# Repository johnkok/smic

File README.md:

# SMIC — 32-channel PDM microphone array and FPGA beamformer

SMIC is an experimental 32-microphone acoustic array built around Infineon
IM72D128V01 PDM microphones and a QMTECH Artix-7 XC7A100T core board. The
repository contains the circular microphone PCB, FPGA RTL, Vivado automation,
simulation testbenches, a C SPI control library, mechanical files, and the
manufacturer reference documents used for the design.

> [!CAUTION]
> The microphone PCB is fully routed, but it is not production-ready. KiCad
> 10.0.8 reports 19 ERC errors, one ERC warning, 32 DRC errors, and 15 DRC
> warnings. The current Gerbers represent the routed geometry but must not be
> fabricated until the footprint, sound-port clearance, bypassing, power/ground
> layout, BOM, and manufacturing release gates are resolved. See
> [SMIC PCB design review](Board/smic/docs/DESIGN_REVIEW.md).

The FPGA prototype has been synthesized, implemented, and loaded into an
XC7A100T, but external interfaces and production-quality audio have not received
complete timing, CDC, or laboratory validation.

## System overview

The intended signal chain is:

```mermaid
flowchart LR
    M[32 IM72D128V01 microphones<br/>16 edge-multiplexed PDM pairs]
    J[SMIC J1<br/>2x20, 1.27 mm]
    U4[QMTECH U4<br/>16 PDM inputs + clock]
    FE[PDM frontend<br/>CIC3 decimation]
    BC[32-channel delay-and-sum<br/>beam core]
    TX[I2S-like or two-slot<br/>audio transmitter]
    HOST[SPI host]
    REG[SPI registers]
    DAI[3.3 V DAI sink]

    M --> J --> U4 --> FE --> BC --> TX --> DAI
    HOST -->|SPI mode 0| REG --> BC
    REG --> TX
```

The FPGA uses a 12.288 MHz external audio reference to generate a 3.072 MHz PDM
clock, 48 kHz PCM samples, and a 3.072 MHz audio bit clock. Each PDM wire carries
two microphones selected on opposite clock edges, giving 32 logical channels
from 16 FPGA inputs.

## Repository layout

| Path | Contents |
|---|---|
| `Board/smic/smic/` | KiCad schematic, PCB, and project files |
| `Board/smic/docs/` | PCB review and exact acoustic-hole coordinates |
| `Board/smic/smic/Gerber/` | Current Gerber/drill export; blocked from fabrication by the design review |
| `FPGA/qmtech_beamformer/rtl/` | Synthesizable-intent SystemVerilog |
| `FPGA/qmtech_beamformer/constraints/` | XC7A100T and connector constraints |
| `FPGA/qmtech_beamformer/scripts/` | Vivado project, synthesis, implementation, and programming automation |
| `FPGA/qmtech_beamformer/sim/` | SPI and beam-core testbenches |
| `FPGA/qmtech_beamformer/host/` | C SPI API and steering helper |
| `FPGA/qmtech_beamformer/docs/` | Detailed FPGA integration notes |
| `Doc/` | QMTECH manuals, microphone datasheet, and array-placement drawing |
| `3D/` | FreeCAD enclosure model and SMIC Experiment workbench |

Generated Vivado projects, compatibility libraries, logs, bitstreams, and local
tool state are ignored and should not be committed.

## Current design status

| Area | Status |
|---|---|
| FPGA synthesis/implementation | Completes for `xc7a100tfgg676-1` with Vivado 2026.1 |
| FPGA SRAM programming | Tested through Vivado Hardware Manager/JTAG |
| FPGA configuration flash | N25Q064A SPIx4 erase/program/verify and flash boot tested; DONE=1 |
| Behavioral simulations | SPI and beam-core tests pass with Icarus Verilog 12 |
| Microphone hole geometry | All 32 NPTHs and back-silkscreen circles match the coordinate CSV |
| Microphone schematic nets | Pin 1 DATA, pin 3 CLOCK, and complementary SELECT pairing verified by source inspection |
| KiCad PCB routing | Fully connected: 954 segments, 287 through vias, three zones, and zero unconnected pads |
| KiCad ERC | **Fail:** 19 errors and one warning; paired PDM outputs need tri-state modeling, power intent and J1 NC need annotation, and the local U1 symbol library is unresolved |
| KiCad DRC | **Fail:** 32 microphone NPTH-to-pad clearance errors and 15 footprint-library mismatch warnings; zero unrouted items |
| Microphone PCB fabrication | **Blocked** pending footprint/clearance resolution, required bypassing, return-path review, released BOM/variant, clean checks, and complete manufacturing output |
| Audio quality | Prototype only; CIC compensation, anti-alias filtering, and protocol validation remain |
| DDR3 | Not instantiated |

## Experimental enclosure

[`3D/main_body.FCStd`](3D/main_body.FCStd) contains a derived
`SMICExperimentalBody` with a 6 mm-pitch internal thread spanning Z=0.8–49.2
mm. The original lower ledge is opened to the 128.4 mm threaded bore so a
bottom cap and separate threaded board-carrier rings can enter from either end.
The exterior uses 24 rounded vertical ribs as an initial wave texture.

The installed **SMIC Experiment** FreeCAD workbench makes the thread pitch,
depth, bore, axial range, bottom opening, and exterior wave count/radius/range
adjustable. Its checked-in source and installation instructions are in
[`3D/FreeCAD/Mod/SMIC_Experiment/`](3D/FreeCAD/Mod/SMIC_Experiment/README.md).
The generated body is a separate feature, leaving the original Part Design
body available for further edits.

[`3D/internal_ring_10mm.FCStd`](3D/internal_ring_10mm.FCStd) is a compatible
10 mm-high carrier ring with a 124 mm opening and 6 mm-pitch male thread. Its
128.0/132.0 mm minor/major diameters provide 0.2 mm radial clearance from the
body on each side, and each thread flank has an additional 0.2 mm axial
printing clearance. The aligned FreeCAD solids have zero interference. The
reproducible generator is [`3D/create_internal_ring.py`](3D/create_internal_ring.py).

### Not yet supplied

Replication still requires engineering work outside the checked-in artifacts:

- A released purchasing BOM with approved manufacturer part numbers.
- A production-reviewed microphone PCB: the current board is routed, but its
  ERC/DRC, microphone footprint, bypassing, return paths, and manufacturing
  package are not released.
- A keyed J1-to-U4 adapter PCB or a fully documented production cable drawing.
- A released enclosure, acoustic baffle, wind protection, mounting hardware,
  and a defined microphone-to-surface port geometry. The checked-in enclosure
  is an adjustable mechanical prototype, not a production release.
- Channel calibration data and a host steering implementation based on the
  actual Fermat coordinates.
- Production tests for supply current, J1 continuity, PDM channels, frequency
  response, noise, sensitivity matching, and beam pattern.
- A project license. No license file is currently present, so obtain permission
  before redistribution or commercial use.

## Required hardware

- QMTECH Artix-7 core board V01 with XC7A100T in the FGG676 package. Verify the
  marking on the fitted FPGA; do not assume another QMTECH variant has the same
  pinout.
- A compatible Xilinx/AMD JTAG programmer. The supplied script uses Vivado
  Hardware Manager, not OpenOCD.
- 32 genuine IM72D128V01 microphones and the remaining PCB components after a
  released BOM has been generated and reviewed.
- Regulated 3.3 V microphone-board supply with sufficient margin and a common
  ground with the FPGA.
- Low-jitter 12.288 MHz, 3.3 V clock source for QMTECH U2-18.
- A 3.3 V SPI controller or correctly selected bidirectional level translators.
- A 3.3 V-compatible DAI receiver, codec, logic analyzer, or oscilloscope.
- A keyed adapter/cable between SMIC J1 and QMTECH U4. Do not connect the two
  headers pin-for-pin; use the mapping below.

For bring-up, use a current-limited bench supply and verify every rail and clock
with an oscilloscope before fitting all microphones or attaching the FPGA.

## Hardware connections

### Complete bench wiring

```mermaid
flowchart TB
    PSU[Regulated 3.3 V supply]
    OSC[12.288 MHz<br/>3.3 V oscillator]
    JTAG[JTAG programmer]
    SPI[SPI controller]
    SINK[DAI receiver / logic analyzer]
    FPGA[QMTECH XC7A100T]
    MIC[SMIC microphone PCB]

    PSU -->|3.3 V: J1-37..40| MIC
    PSU ---|common ground| FPGA
    OSC -->|U2-18| FPGA
    JTAG -->|JTAG header| FPGA
    SPI <-->|U2 SPI, 3.3 V| FPGA
    FPGA -->|U2 BCLK / FS / SD| SINK
    FPGA -->|U4-21 to J1-2: PDM_CLK| MIC
    MIC -->|J1-6..36 even to U4-5..20: PDM_DATA| FPGA
```

All external interfaces in the current configuration are 3.3 V. QMTECH U2 is
in FPGA bank 15 and cannot be converted to 1.8 V by changing only the XDC
`IOSTANDARD`. A 1.8 V host requires physical translators.

### SMIC J1 to QMTECH U4

The adapter preserves channel order but changes pin numbering:

| Function | SMIC J1 | QMTECH U4 | FPGA pin | RTL port |
|---|---:|---:|---|---|
| PDM clock | 2 | 21 | F2 | `pdm_clk` |
| Pair 1 | 6 | 5 | B5 | `pdm_data[0]` |
| Pair 2 | 8 | 6 | A5 | `pdm_data[1]` |
| Pair 3 | 10 | 7 | B4 | `pdm_data[2]` |
| Pair 4 | 12 | 8 | A4 | `pdm_data[3]` |
| Pair 5 | 14 | 9 | A3 | `pdm_data[4]` |
| Pair 6 | 16 | 10 | A2 | `pdm_data[5]` |
| Pair 7 | 18 | 11 | D4 | `pdm_data[6]` |
| Pair 8 | 20 | 12 | C4 | `pdm_data[7]` |
| Pair 9 | 22 | 13 | C2 | `pdm_data[8]` |
| Pair 10 | 24 | 14 | B2 | `pdm_data[9]` |
| Pair 11 | 26 | 15 | E5 | `pdm_data[10]` |
| Pair 12 | 28 | 16 | D5 | `pdm_data[11]` |
| Pair 13 | 30 | 17 | C1 | `pdm_data[12]` |
| Pair 14 | 32 | 18 | B1 | `pdm_data[13]` |
| Pair 15 | 34 | 19 | E1 | `pdm_data[14]` |
| Pair 16 | 36 | 20 | D1 | `pdm_data[15]` |

J1 odd pins 1 through 35 are ground returns. J1-4 is not connected. J1-37
through J1-40 are the external 3.3 V input. U4 does not supply microphone-board
power: U4-3/4 are VCCO configuration points and U4-63/64 are `VIN`; neither is
an acceptable substitute for the separate regulated microphone supply.

### QMTECH U2: SPI, DAI, reset, and reference clock

| U2 | FPGA pin | Direction at FPGA | Function |
|---:|---|---|---|
| 20 | H21 | Input | SPI SCK |
| 6 | E26 | Input | SPI CS, active-low |
| 7 | D25 | Input | SPI MOSI |
| 8 | E25 | Output | SPI MISO |
| 9 | G26 | Output | Audio BCLK |
| 10 | H26 | Output | Audio frame sync |
| 11 | E23 | Output | Audio serial data |
| 12 | F23 | Input | Reset, active-low; internal pull-up |
| 18 | G20 | Input | External 12.288 MHz reference |

The onboard LEDs are active-low: D5 flashes at 1 Hz while the beamformer is
enabled, and D6 illuminates for at least 100 ms after a complete SPI access.

## Microphone PCB

### Geometry

The PCB is a two-layer, 1.6 mm circular design. The Edge.Cuts source circle is
centered at `(114.205281, 98.532588)` mm. Microphones follow the Fermat layout
shown in `Doc/DMIC_placement.jpeg`.

The IM72D128V01 PG-LLGA-5-3 recommendation uses a 0.8 mm acoustic hole at a
0.68 mm local-X offset from the package origin. Each package origin is shifted
to put its actual NPTH on the nominal Fermat point, and every DMIC body is
horizontal or vertical. All 32 NPTHs and their back-silkscreen circles match
[mic_acoustic_holes.csv](Board/smic/docs/mic_acoustic_holes.csv). Use those CSV
coordinates, not reference-designator origins, for calibration and beamforming.

### 3.3 V population

For direct compatibility with the FPGA:

- Do not populate U2 (`LP5907MFX-1.8`).
- Populate R18 as 0 ohm to use the existing regulator-bypass path.
- Supply exactly 3.3 V through J1-37..40.
- Never populate U2 and the R18 bypass simultaneously.

U1 is the 74FCT3807S clock fanout. R1 through R17 are 22 ohm series resistors;
the PCB contains 36 nominal 0.1 µF capacitors and two nominal 1 µF capacitors.
These values are a design summary, not a released purchasing BOM. Confirm
manufacturer part numbers, packages, ratings, availability, polarity, assembly
rules, and the exact U1 variant before ordering.

The two 1 µF parts do not satisfy the microphone datasheet's instruction to
place a 1 µF bypass capacitor close to each microphone VDD pad. This and the
U1 decoupling placement are production blockers, even though all power nets are
routed. The 74FCT3807S family supports 3.3 V, but an exact orderable TSSOP-20
part number must be selected.

### Current PCB review and required work

The current schematic-derived net assignments correctly connect IM72D128V01
pin 1 to paired DATA nets and pin 3 to U1 clock branches. Each of the 16 DATA
nets has two microphones with complementary SELECT straps. All ten U1 outputs
are used. The PCB has 954 track segments and 287 through vias, and KiCad reports
zero unconnected pads after zone refill.

Connectivity is not a production sign-off. KiCad 10.0.8 currently reports 19
ERC errors plus one warning and 32 DRC errors plus 15 warnings. The DRC errors
are the 0.18 mm copper-to-acoustic-NPTH clearance at all 32 microphones versus
the configured 0.25 mm minimum. The warnings are local microphone-footprint
library mismatches. The generated Gerbers and drills reflect this blocked
design and must not be ordered.

The detailed [schematic and PCB review](Board/smic/docs/DESIGN_REVIEW.md)
prioritizes these revisions before production release:

- create and freeze the correct project-local PG-LLGA-5-3 microphone footprint,
  then resolve the 32 acoustic-hole clearance errors with the fabricator;
- add the required 1 µF local bypassing at every microphone and move U1's four
  local capacitors directly to its supply/ground pairs;
- model the paired PDM outputs as tri-state, annotate power and no-connect
  intent, fix the missing local symbol-library mapping, and obtain clean ERC;
- preserve a continuous ground return, preferably with a four-layer stackup,
  instead of relying on the split B.Cu GND/3.3 V plane and stitching vias;
- review all ten clock branches, test-point stubs, and optional source damping
  using oscilloscope measurements rather than connectivity alone;
- add connector-side bulk capacitance and optional filtering/protection;
- key the board-to-FPGA interconnect and improve test access;
- add assembly fiducials plus enclosure-compatible mounting/tooling features;
- add a board revision, voltage/variant markings, approved MPNs, position files,
  and fabrication/assembly drawings.

These are design recommendations, not implemented hardware changes. Reassess
component placement and acoustic cavities against the enclosure before release.

### Manufacturing release checklist

1. Freeze the exact 3.3 V assembly variant, MPNs, project-local symbol library,
   and corrected PG-LLGA-5-3 footprint.
2. Add the required microphone/U1 bypassing and approve power/ground return
   paths, clock routing, connector protection, fiducials, and mechanics.
3. Resolve ERC by modeling real electrical intent; do not broadly exclude the
   paired PDM output errors.
4. Resolve every microphone hole-clearance finding with the fabricator, remove
   stale exclusions, refill zones, and obtain reviewed clean ERC/DRC results.
5. Re-verify J1 mapping, SELECT polarity, all clock destinations, and every
   acoustic NPTH against `mic_acoustic_holes.csv`.
6. Inspect solder-mask and paste apertures against the microphone datasheet.
7. Add revision/voltage/variant markings and complete fabrication, assembly,
   acoustic-port handling, and test specifications.
8. Generate schematic PDF, released BOM, position files, Gerbers, drills,
   Gerber job, and optional IPC-356 from one tagged revision.
9. Review all outputs in an independent viewer and compare their netlist and
   drill counts with the KiCad source.
10. Fabricate a small pilot batch, inspect ports and reflow, and test supply,
    clocks, all 16 PDM pairs, channel order, noise, calibration, and beam pattern
    before authorizing production quantity.

The checked-in `Board/smic/smic/Gerber/` directory was regenerated from the
current routed board, but it is explicitly blocked by the findings above and
must not yet be sent to a manufacturer.

## FPGA development

### Tool requirements

- AMD/Xilinx Vivado 2026.1 installed at `/opt/AMD_II/2026.1/Vivado`.
- Bash, Tcl, and standard Linux build utilities.
- Icarus Verilog 12 or another SystemVerilog simulator for the included tests.
- `curl`, `sha256sum`, and `dpkg-deb` only if the Ubuntu compatibility setup is
  needed.

To use another Vivado installation, edit `SMIC_VIVADO_ROOT` in
`FPGA/qmtech_beamformer/scripts/run_vivado.sh`.

### Run simulations

From the repository root:

```bash
iverilog -g2012 -s tb_spi -o /tmp/smic_tb_spi \
  FPGA/qmtech_beamformer/rtl/spi_regs.sv \
  FPGA/qmtech_beamformer/sim/tb_spi.sv
vvp /tmp/smic_tb_spi

iverilog -g2012 -s tb_beamformer -o /tmp/smic_tb_beamformer \
  FPGA/qmtech_beamformer/rtl/beam_core.sv \
  FPGA/qmtech_beamformer/sim/tb_beamformer.sv
vvp /tmp/smic_tb_beamformer
```

Both tests should print `PASS`. They cover register writes/commit/access and the
beam-core frame deadline, normalization, and integer delay path; they are not a
complete top-level, PDM, audio-protocol, timing, or CDC verification suite.

### Create, synthesize, and build

```bash
cd FPGA/qmtech_beamformer

# Only if Vivado reports missing legacy ncurses/tinfo libraries:
./scripts/setup_vivado_compat.sh

./scripts/run_vivado.sh -mode batch -source scripts/create_vivado_project.tcl
./scripts/run_vivado.sh -mode batch -source scripts/synthesize.tcl
./scripts/run_vivado.sh -mode batch -source scripts/build_bitstream.tcl
```

Review at least these generated reports before programming:

- `vivado_project/synth_utilization.rpt`
- `vivado_project/synth_timing_summary.rpt`
- `vivado_project/impl_utilization.rpt`
- `vivado_project/impl_timing_summary.rpt`
- `vivado_project/impl_drc.rpt`

The expected bitstream is
`vivado_project/qmtech_beamformer.runs/impl_1/beamformer_top.bit`.

### Program volatile FPGA SRAM

Connect exactly one compatible JTAG target, power the QMTECH board, then run:

```bash
cd FPGA/qmtech_beamformer
./scripts/run_vivado.sh -mode batch -source scripts/program_device.tcl
```

The script enumerates the chain, requires exactly one XC7A100T, programs the
bitstream, and reports DONE when that property is available. Programming is
volatile and is lost when power is removed.

### Program nonvolatile configuration flash

The QMTECH V01 board uses a 3.3 V Micron N25Q064A, 64 Mbit configuration flash.
The checked-in constraints generate a Master-SPIx4 bitstream matching the
board's `M[2:0]=100` boot straps. To replace the board's power-on image:

```bash
cd FPGA/qmtech_beamformer
./scripts/run_vivado.sh -mode batch -source scripts/generate_cfgmem.tcl
./scripts/run_vivado.sh -mode batch -source scripts/program_cfgmem.tcl
```

The programming script requires exactly one XC7A100T, loads Vivado's temporary
SPI bridge, erases the existing flash image, programs the MCS file, performs a
read-back verification, and boots the FPGA from flash. On 2026-11-15 the board
reported JEDEC ID `20 BA 17`, program/verify completed successfully, and the
flash-booted FPGA reported `DONE=1`.

## Operating the beamformer

### SPI protocol

- Use **SPI mode 0**: `CPOL=0`, `CPHA=0`. SCK idles low; the FPGA samples
  MOSI on rising edges and the host samples MISO on rising edges. Change data
  on falling edges.
- Use MSB first and keep SCK at or below 2 MHz. This conservative limit is for
  the current SCK-to-12.288-MHz toggle synchronizer, not the FPGA I/O limit.
- `CS_N` is active low. Hold it low for exactly 56 clocks and return it high
  between commands. MISO is high-impedance while `CS_N` is high, so the bus may
  be shared.
- Every command is exactly seven bytes:

```text
byte 0       byte 1..2             byte 3..6
opcode       16-bit address        32-bit data
0x02 write   big-endian            big-endian
0x03 read    big-endian            returned big-endian
```

For a write, opcode `0x02` is followed by the address and value. For a read,
send opcode `0x03`, the address, and four dummy bytes; the returned value is in
receive bytes 3 through 6. A command is accepted only after all 56 bits arrive.
The host transfer callback must keep `CS_N` active across the whole seven-byte
exchange and must not split it into separate opcode/address/data transfers.

Register writes cross asynchronously into the audio clock domain and normally
become visible within three 12.288 MHz clocks. Delay, gain, and polarity writes
go to shadow registers; writing `COMMIT.bit0=1` copies the complete set into the
beamformer together. Readback of those fields reports the shadow value. D6 is
held on for about 100 ms after every valid read or write transaction.

### Important registers

| Address | Name | Description |
|---:|---|---|
| `0x0000` | ID | Read-only, expected `0xBF320001` |
| `0x0004` | CTRL | Bit 0 enable, bit 1 mute |
| `0x0008` | STATUS | Placeholder |
| `0x000C` | SAMPLE_RATE | Read-only 48000 |
| `0x0010` | MODE | Bit 1 selects two-slot TDM-like output |
| `0x0014` | AZIMUTH | Reserved; host currently calculates delays |
| `0x0018` | ELEVATION | Reserved; host currently calculates delays |
| `0x001C` | OUTPUT_GAIN | Q1.15 |
| `0x0020` | ENABLE_MASK | One bit per microphone |
| `0x0024` | COMMIT | Write bit 0 to activate shadow delays, gains, and polarity |
| `0x0028` | FRAME_COUNT | Output frame counter |
| `0x002C` | ERRORS | Placeholder |
| `0x0030` | TEST_CONTROL | Test-source enable, routing, and pattern |
| `0x0034` | TEST_AMPLITUDE | Signed 24-bit synthetic PCM amplitude |
| `0x0038` | POLARITY_MASK | One invert bit per channel; shadowed by `COMMIT` |
| `0x0100 + 4*i` | DELAY[i] | Q16.16 samples, integer part limited to 254 |
| `0x0200 + 4*i` | GAIN[i] | Q1.15 microphone gain |
| `0x0300 + 4*i` | LEVEL[i] | Per-channel level |

`MODE.bit1` selects the two-slot TDM-like transmitter; zero selects I2S-like
framing. All other `MODE` bits are reserved and should be written as zero.
`OUTPUT_GAIN` and `GAIN[i]` use unsigned Q1.15 (`0x8000` = 1.0). Values up to
`0xFFFF` are valid, although headroom must be allowed to avoid output clipping.
Only `TEST_AMPLITUDE[23:0]` is used and it is interpreted as signed two's
complement; bits 31:24 are ignored and should be written as zero.
`LEVEL[i]` is the absolute magnitude of the most recently accepted PCM sample,
not RMS or peak-hold metering.

`TEST_CONTROL` is defined as follows:

| Bits | Meaning |
|---:|---|
| 0 | Enable synthetic PCM and bypass the PDM samples |
| 1 | Send the test signal to all channels; if zero, use the selected channel |
| 6:2 | Selected channel, 0 through 31 |
| 9:8 | Pattern: 0 = 1 kHz square, 1 = 1 kHz impulse train, 2 = DC, 3 = alternating samples (24 kHz) |
| Other | Reserved, write zero |

When test mode is enabled, unselected channels are forced to zero. The source
enters after PDM decimation but before history, fractional delay, calibration,
summation, and audio transmission. It therefore tests the beamformer and output
path, but does **not** test microphones, PDM wiring, CIC decimation, or acoustic
channel order.

### C host API

Implement `bf_spi_transfer`, initialize a `bf_device`, and call:

```c
bf_device dev = {
    .transfer = platform_spi_transfer,
    .ctx = &platform_context,
};

bf_init(&dev, array_radius_m);
bf_set_geometry(&dev, measured_positions);
bf_set_calibration(&dev, measured_calibration);
bf_set_direction(&dev, azimuth_deg, elevation_deg);
bf_start(&dev);
```

`bf_init()` supplies a circular fallback geometry only. The PCB is a Fermat
spiral, so production software must build a 32-element `bf_mic_position` array
from `Board/smic/docs/mic_acoustic_holes.csv`, convert millimetres to metres,
subtract the array centre, choose whether acoustic +Y is KiCad +Y or -Y, and
call `bf_set_geometry()`. The `MKn` number is treated as channel `n-1` by the
heatmap tool, but that assumption must be verified against the physical PDM
pair/edge channel order before use.

The host library stores per-channel gain, delay correction, and polarity in
`bf_mic_calibration`. `bf_set_direction()` combines those values with geometric
steering, writes all shadow registers, writes the polarity mask, then commits
the set. These values are volatile: reload geometry and calibration after every
FPGA reset or power cycle.

### Steering mathematics

Angles use degrees. Azimuth is measured in the array XY plane from +X toward
+Y; elevation is measured from the XY plane toward +Z. The look-direction unit
vector is

```text
u = [cos(el) cos(az), cos(el) sin(az), sin(el)].
```

For microphone position `r_i=[x_i,y_i,z_i]`, sample rate `Fs=48000`, and speed
of sound `c` (343 m/s by default), the host first calculates

```text
p_i       = dot(r_i, u)
raw_i     = -Fs * p_i / c + calibration_delay_i
d_i       = raw_i - min(raw_0 ... raw_31)
DELAY[i]  = round(65536 * d_i)
GAIN[i]   = round(32768 * calibration_gain_i)
```

Subtracting the common minimum makes every hardware delay non-negative without
changing relative phase. `d_i` must be at most 254 samples. At 48 kHz that is
5.29 ms, much longer than the geometric delay across this PCB. Temperature
changes `c`; for tighter steering, use approximately
`c = 331.3 + 0.606*T_C` m/s or a measured local value.

Inside `beam_core.sv`, the integer and fractional portions select two adjacent
history samples. With `f=DELAY[i][15:0]/65536`, interpolation is

```text
x_i' = (1-f) * history_i[n-floor(d_i)]
       + f * history_i[n-floor(d_i)-1]
y    = OUTPUT_GAIN * (sum(enabled_i * polarity_i * GAIN[i] * x_i') / N)
```

`N` is the number of enabled microphones and division uses a Q0.24 reciprocal
lookup table. The final value is saturated to signed 24-bit PCM. Linear
interpolation is inexpensive but its high-frequency magnitude/phase error is
larger than a Farrow or windowed-sinc fractional-delay filter.

### Beam heatmap

The FPGA produces one audio beam; it does not render or scan a heatmap. The
far-field prediction is implemented on the host in
[`beam_heatmap.py`](FPGA/qmtech_beamformer/host/beam_heatmap.py). It uses the
actual acoustic-hole coordinates, the same steering-delay equation, optional
calibration, and the narrow-band array factor at a chosen frequency. Run:

```bash
python3 FPGA/qmtech_beamformer/host/beam_heatmap.py \
  --geometry Board/smic/docs/mic_acoustic_holes.csv \
  --calibration FPGA/qmtech_beamformer/host/calibration.example.csv \
  --frequency 3000 --steer-az 45 --steer-el 0 \
  --output /tmp/smic_3khz
```

This writes `/tmp/smic_3khz.csv` in dB and a directly viewable
`/tmp/smic_3khz.svg`. By default KiCad Y is negated so +Y points upward in a
top-view Cartesian plot; pass `--keep-kicad-y` to retain KiCad's Y direction.
The result is a theoretical free-field map, not measured acoustic performance:
it omits enclosure diffraction, microphone directivity, tolerances, reflections,
and the CIC response. A broadband beam must be assessed at several frequencies.

### Digital test mode

Use test mode before attaching the microphone PCB to check SPI, shadow commits,
delay/gain/polarity processing, DAI, and the receiver:

```c
/* 0x040000 is about -30 dBFS in signed 24-bit PCM. */
bf_set_test_mode(&dev, BF_TEST_SQUARE_1KHZ, 0, 1, 0x040000);
bf_start(&dev);
/* Inspect audio output, then always return to real PDM input. */
bf_disable_test_mode(&dev);
```

With `all_channels=1` and zero delays, output amplitude should equal the test
amplitude because the core normalizes by enabled-channel count. Select a single
channel and set `ENABLE_MASK` to the same one bit to test that channel's delay,
gain, and polarity without the other 31 zeros reducing the result. The impulse
pattern is useful for confirming integer/fractional delay. DC is intended for
short datapath checks and should not be sent to speakers at high amplitude.

### Microphone calibration guide

Calibration support is manual/offline; the design does not yet estimate
coefficients automatically. A practical procedure is:

1. Verify channel order first with a close sound source at each microphone.
   Record the FPGA channel corresponding to every `MKn`; do not infer it only
   from connector numbering or shared PDM data pairs.
2. Place the completed array and a reference loudspeaker in a low-reflection
   setup, aimed normal to the PCB and far enough away that path differences are
   small. Keep source, gain, and geometry fixed.
3. Capture every decimated microphone channel using an FPGA diagnostic build or
   external logic. The current mono audio output and instantaneous `LEVEL[i]`
   registers are not sufficient for accurate phase calibration.
4. Play a band-limited sweep or maximum-length sequence. Estimate relative lag
   by cross-correlation around the expected geometric lag. Choose a reference
   channel and store each residual in `delay_samples`; fractional values are
   supported.
5. Compare RMS amplitudes over the same steady segment. Set
   `gain_linear_i = target_rms / measured_rms_i`, then reduce all gains by a
   common factor if any would reach 2.0. Use `invert=1` only when correlation
   shows a true 180-degree polarity reversal.
6. Save 32 rows using the format in
   [`calibration.example.csv`](FPGA/qmtech_beamformer/host/calibration.example.csv),
   load them into `bf_mic_calibration`, call `bf_set_calibration()`, and then
   call `bf_set_direction()` to write and commit the combined coefficients.
7. Repeat the measurement from several directions and across the operating
   band. A delay that changes strongly with frequency indicates acoustic or
   filter mismatch that a single delay/gain coefficient cannot correct.

Calibration delay is a correction applied by the FPGA. If a channel is measured
late by `q` samples, store approximately `-q` for that channel; removal of the
common minimum then delays the other channels by the equivalent amount. If it
is early by `q`, store approximately `+q`. Confirm this sign convention with an
impulse or correlation before saving coefficients. Negative values are accepted
as long as the final relative delays fit the 254-sample history limit.

### Audio output

The output uses 64 bit clocks per 48 kHz frame. Mode bit 1 selects between an
I2S-like framing mode and a TDM-like two-slot mode. Only one mono beam is emitted
in slot 0; slot 1 is zero. Validate BCLK, frame-sync polarity, sample alignment,
and one-bit I2S delay against the actual receiver before relying on the stream.

## Signal-processing architecture and limitations

- PDM decimation is CIC3 at a factor of 64. It requires a compensation and
  anti-alias FIR for production-quality audio.
- The beamformer uses a time-multiplexed 8192x24 history memory and completes a
  frame in 195 of the 256 available 12.288 MHz clocks.
- Fractional delay uses an initial linear method; a verified higher-quality
  interpolator is still required.
- There is no AEC, AGC, automatic microphone calibration, MVDR, source tracking,
  or multiple simultaneous beams.
- The planar array cannot uniquely resolve elevation sign and may exhibit
  front/back ambiguity depending on its acoustic mounting.
- External I/O delays and complete CDC constraints are not signed off.
- DDR3 is intentionally unused because the present history is only 24 KiB.
  DDR3 is a future option for capture buffers, longer delays, diagnostics, or
  multiple beams and requires a board-specific MIG configuration.

## Bring-up sequence

1. Resolve the production-review blockers and manufacture only a tagged,
   reviewed microphone PCB; do not use the current blocked Gerbers.
2. With U2 absent and R18 fitted, power only the microphone PCB from a
   current-limited 3.3 V supply. Verify resistance-to-ground before power and
   then verify the rail at U1 and several microphones.
3. Apply the PDM clock independently and confirm all fanout outputs before
   attaching the FPGA data inputs.
4. Verify J1 pin 1, cable orientation, and every continuity path to U4.
5. Program the FPGA with the microphone PCB disconnected and confirm D5/D6,
   SPI ID access, clock, reset, and DAI outputs.
6. Connect one microphone pair first. Confirm clock amplitude, DATA high-Z edge
   behavior, channel polarity, and PCM activity.
7. Add the remaining pairs while monitoring supply current and signal integrity.
8. Measure channel order using a local acoustic stimulus and compare it with the
   CSV geometry before enabling beam steering.
9. Capture known signals, check clipping/noise/CIC droop, and calibrate gain and
   delay before evaluating beam patterns.

## Primary references

- [FPGA integration and limitations](FPGA/qmtech_beamformer/docs/INTEGRATION.md)
- [Microphone PCB review](Board/smic/docs/DESIGN_REVIEW.md)
- [Exact acoustic-hole coordinates](Board/smic/docs/mic_acoustic_holes.csv)
- `Doc/infineon_im72d128_datasheet_en.pdf`
- `Doc/QMTECH_Artix-7_XC7A100T_Core_Board_User_Manual(Hardware)_V01.pdf`
- `Doc/QMTECH_XC7A75T_100T_200T-CORE-BOARD-V01-20210109.pdf`

Before changing connector assignments, voltage levels, the FPGA part, or the
microphone footprint, recheck the original manufacturer documents rather than
copying values from this README alone.

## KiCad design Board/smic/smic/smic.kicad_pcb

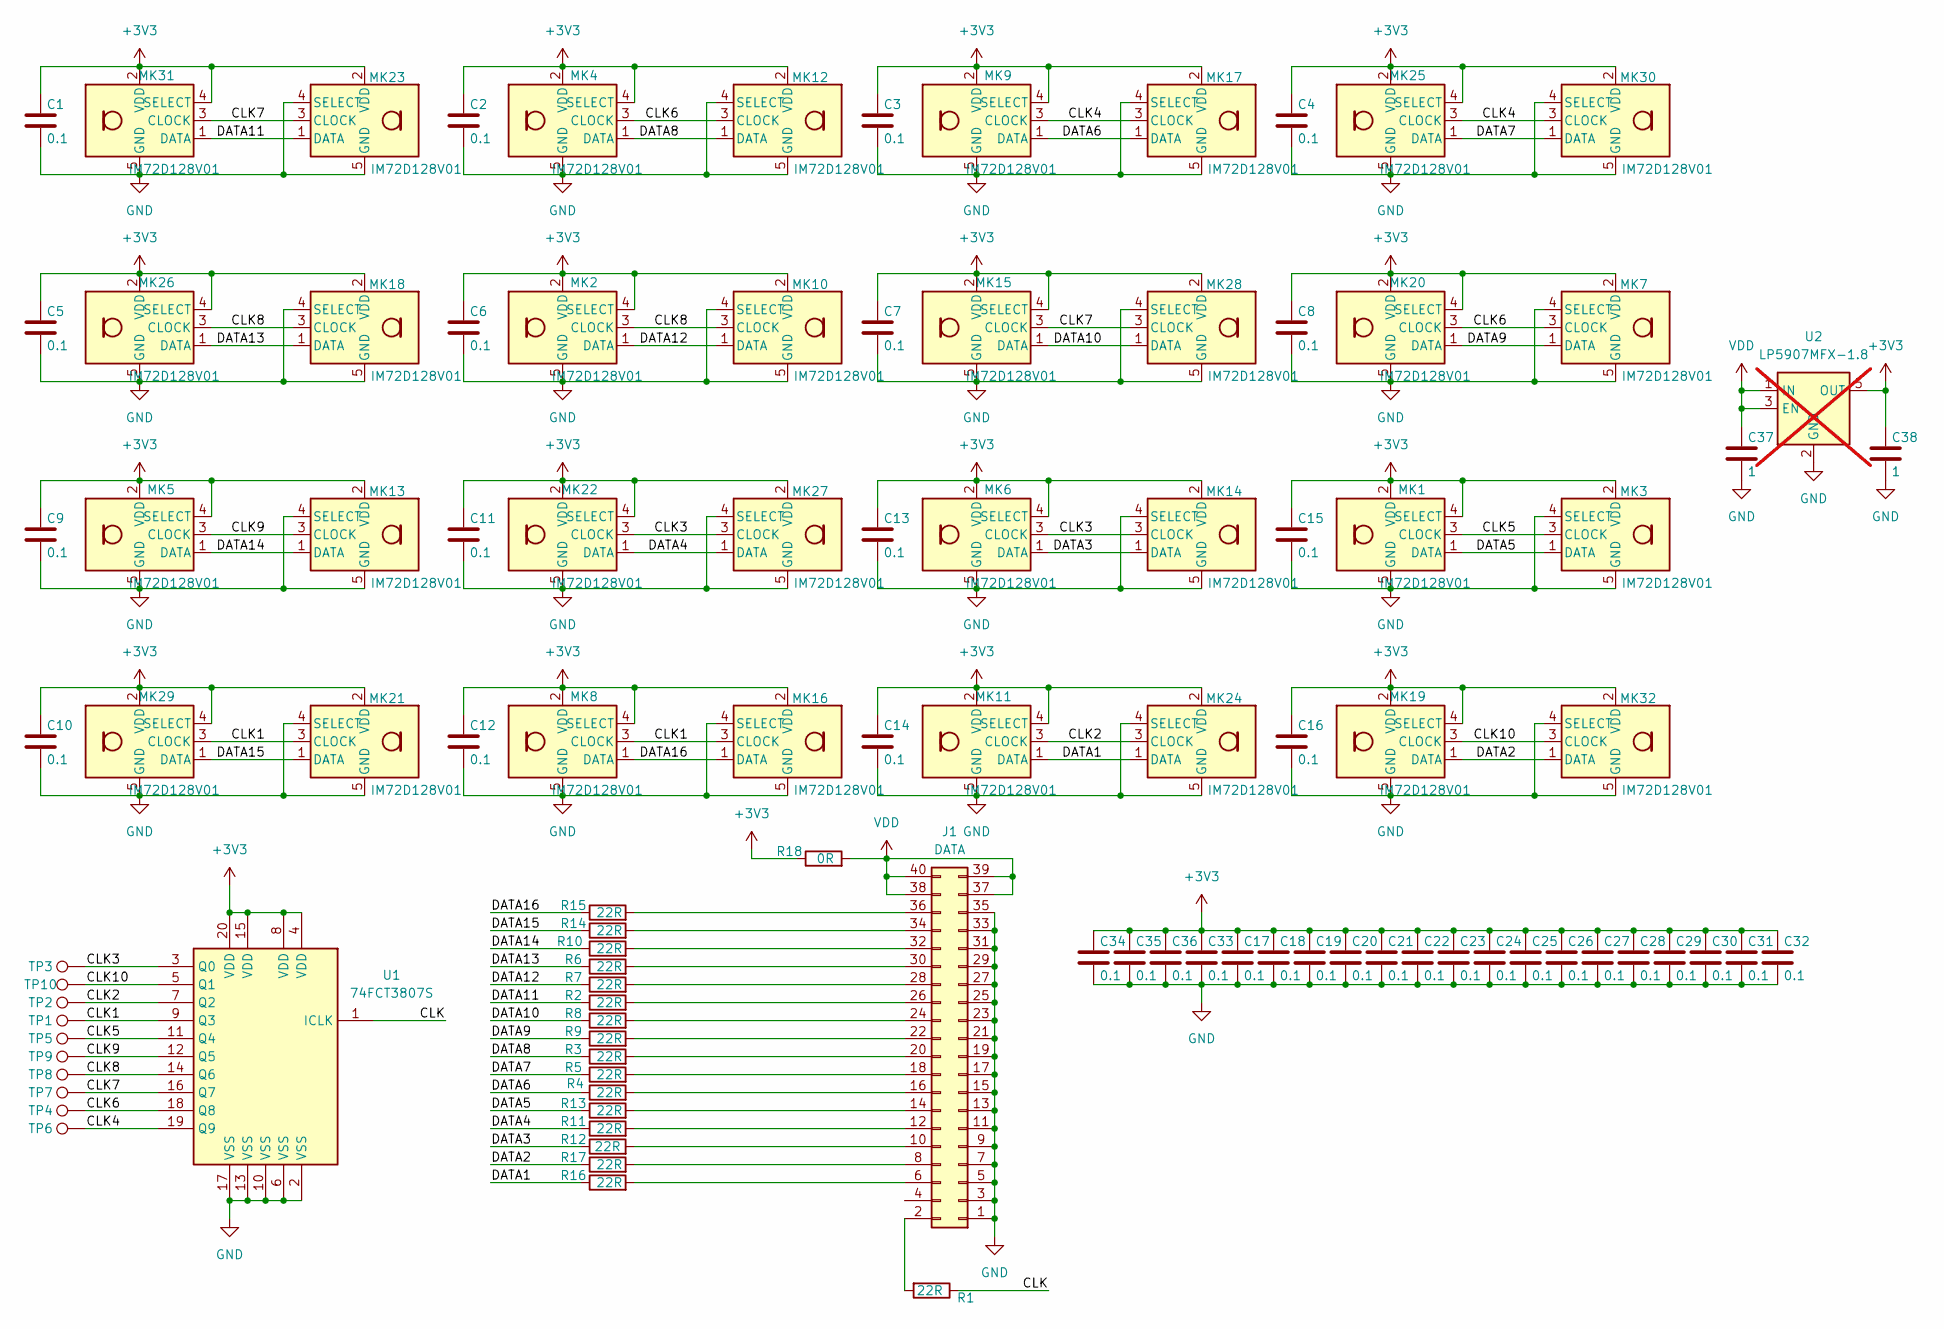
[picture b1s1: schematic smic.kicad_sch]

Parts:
C1, C2, C3, C4, C5, C6, C7, C8, C9, C10, C11, C12, C13, C14, C15, C16, C17, C18, C19, C20, C21, C22, C23, C24, C25, C26, C27, C28, C29, C30, C31, C32, C33, C34, C35, C36: 0.1; C_0603_1608Metric
C37, C38: 1; C_0805_2012Metric_Pad1.18x1.45mm_HandSolder
J1: DATA; PinHeader_2x20_P1.27mm_Vertical_SMD
MK1, MK2, MK3, MK4, MK5, MK6, MK7, MK8, MK9, MK10, MK11, MK12, MK13, MK14, MK15, MK16, MK17, MK18, MK19, MK20, MK21, MK22, MK23, MK24, MK25, MK26, MK27, MK28, MK29, MK30, MK31, MK32: IM72D128V01; Infineon_PG-LLGA-5-2
R1, R2, R3, R4, R5, R6, R7, R8, R9, R10, R11, R12, R13, R14, R15, R16, R17: 22R; R_0603_1608Metric_Pad0.98x0.95mm_HandSolder
R18: 0R; R_1206_3216Metric_Pad1.30x1.75mm_HandSolder
TP1, TP2, TP3, TP4, TP5, TP6, TP7, TP8, TP9, TP10: TestPoint_Pad_D1.5mm
U1: 74FCT3807S; TSSOP-20_4.4x6.5mm_P0.65mm
U2: LP5907MFX-1.8; SOT-23-5; not fitted

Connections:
+3V3: C1.2, C2.2, C3.2, C4.2, C5.2, C6.2, C7.2, C8.2, C9.2, C10.2, C11.2, C12.2, C13.2, C14.2, C15.2, C16.2, C17.2, C18.2, C19.2, C20.2, C21.2, C22.2, C23.2, C24.2, C25.2, C26.2, C27.2, C28.2, C29.2, C30.2, C31.2, C32.2, C33.2, C34.2, C35.2, C36.2, C38.2, MK1.2 (VDD), MK1.4 (SELECT), MK2.2 (VDD), MK2.4 (SELECT), MK3.2 (VDD), MK4.2 (VDD), MK4.4 (SELECT), MK5.2 (VDD), MK5.4 (SELECT), MK6.2 (VDD), MK6.4 (SELECT), MK7.2 (VDD), MK8.2 (VDD), MK8.4 (SELECT), MK9.2 (VDD), MK9.4 (SELECT), MK10.2 (VDD), MK11.2 (VDD), MK11.4 (SELECT), MK12.2 (VDD), MK13.2 (VDD), MK14.2 (VDD), MK15.2 (VDD), MK15.4 (SELECT), MK16.2 (VDD), MK17.2 (VDD), MK18.2 (VDD), MK19.2 (VDD), MK19.4 (SELECT), MK20.2 (VDD), MK20.4 (SELECT), MK21.2 (VDD), MK22.2 (VDD), MK22.4 (SELECT), MK23.2 (VDD), MK24.2 (VDD), MK25.2 (VDD), MK25.4 (SELECT), MK26.2 (VDD), MK26.4 (SELECT), MK27.2 (VDD), MK28.2 (VDD), MK29.2 (VDD), MK29.4 (SELECT), MK30.2 (VDD), MK31.2 (VDD), MK31.4 (SELECT), MK32.2 (VDD), R18.1, U1.4 (VDD), U1.8 (VDD), U1.15 (VDD), U1.20 (VDD), U2.5 (OUT)
/CLK: R1.1, U1.1 (ICLK)
/CLK1: MK8.3 (CLOCK), MK16.3 (CLOCK), MK21.3 (CLOCK), MK29.3 (CLOCK), TP1.1 (1_1), U1.9 (Q3)
/CLK2: MK11.3 (CLOCK), MK24.3 (CLOCK), TP2.1 (1_1), U1.7 (Q2)
/CLK3: MK6.3 (CLOCK), MK14.3 (CLOCK), MK22.3 (CLOCK), MK27.3 (CLOCK), TP3.1 (1_1), U1.3 (Q0)
/CLK4: MK9.3 (CLOCK), MK17.3 (CLOCK), MK25.3 (CLOCK), MK30.3 (CLOCK), TP6.1 (1_1), U1.19 (Q9)
/CLK5: MK1.3 (CLOCK), MK3.3 (CLOCK), TP5.1 (1_1), U1.11 (Q4)
/CLK6: MK4.3 (CLOCK), MK7.3 (CLOCK), MK12.3 (CLOCK), MK20.3 (CLOCK), TP4.1 (1_1), U1.18 (Q8)
/CLK7: MK15.3 (CLOCK), MK23.3 (CLOCK), MK28.3 (CLOCK), MK31.3 (CLOCK), TP7.1 (1_1), U1.16 (Q7)
/CLK8: MK2.3 (CLOCK), MK10.3 (CLOCK), MK18.3 (CLOCK), MK26.3 (CLOCK), TP8.1 (1_1), U1.14 (Q6)
/CLK9: MK5.3 (CLOCK), MK13.3 (CLOCK), TP9.1 (1_1), U1.12 (Q5)
/CLK10: MK19.3 (CLOCK), MK32.3 (CLOCK), TP10.1 (1_1), U1.5 (Q1)
/DATA1: MK11.1 (DATA), MK24.1 (DATA), R16.1
/DATA2: MK19.1 (DATA), MK32.1 (DATA), R17.1
/DATA3: MK6.1 (DATA), MK14.1 (DATA), R12.1
/DATA4: MK22.1 (DATA), MK27.1 (DATA), R11.1
/DATA5: MK1.1 (DATA), MK3.1 (DATA), R13.1
/DATA6: MK9.1 (DATA), MK17.1 (DATA), R4.1
/DATA7: MK25.1 (DATA), MK30.1 (DATA), R5.1
/DATA8: MK4.1 (DATA), MK12.1 (DATA), R3.1
/DATA9: MK7.1 (DATA), MK20.1 (DATA), R9.1
/DATA10: MK15.1 (DATA), MK28.1 (DATA), R8.1
/DATA11: MK23.1 (DATA), MK31.1 (DATA), R2.1
/DATA12: MK2.1 (DATA), MK10.1 (DATA), R7.1
/DATA13: MK18.1 (DATA), MK26.1 (DATA), R6.1
/DATA14: MK5.1 (DATA), MK13.1 (DATA), R10.1
/DATA15: MK21.1 (DATA), MK29.1 (DATA), R14.1
/DATA16: MK8.1 (DATA), MK16.1 (DATA), R15.1
GND: C1.1, C2.1, C3.1, C4.1, C5.1, C6.1, C7.1, C8.1, C9.1, C10.1, C11.1, C12.1, C13.1, C14.1, C15.1, C16.1, C17.1, C18.1, C19.1, C20.1, C21.1, C22.1, C23.1, C24.1, C25.1, C26.1, C27.1, C28.1, C29.1, C30.1, C31.1, C32.1, C33.1, C34.1, C35.1, C36.1, C37.1, C38.1, J1.1, J1.3, J1.5, J1.7, J1.9, J1.11, J1.13, J1.15, J1.17, J1.19, J1.21, J1.23, J1.25, J1.27, J1.29, J1.31, J1.33, J1.35, MK1.5 (GND), MK2.5 (GND), MK3.4 (SELECT), MK3.5 (GND), MK4.5 (GND), MK5.5 (GND), MK6.5 (GND), MK7.4 (SELECT), MK7.5 (GND), MK8.5 (GND), MK9.5 (GND), MK10.4 (SELECT), MK10.5 (GND), MK11.5 (GND), MK12.4 (SELECT), MK12.5 (GND), MK13.4 (SELECT), MK13.5 (GND), MK14.4 (SELECT), MK14.5 (GND), MK15.5 (GND), MK16.4 (SELECT), MK16.5 (GND), MK17.4 (SELECT), MK17.5 (GND), MK18.4 (SELECT), MK18.5 (GND), MK19.5 (GND), MK20.5 (GND), MK21.4 (SELECT), MK21.5 (GND), MK22.5 (GND), MK23.4 (SELECT), MK23.5 (GND), MK24.4 (SELECT), MK24.5 (GND), MK25.5 (GND), MK26.5 (GND), MK27.4 (SELECT), MK27.5 (GND), MK28.4 (SELECT), MK28.5 (GND), MK29.5 (GND), MK30.4 (SELECT), MK30.5 (GND), MK31.5 (GND), MK32.4 (SELECT), MK32.5 (GND), U1.2 (VSS), U1.6 (VSS), U1.10 (VSS), U1.13 (VSS), U1.17 (VSS), U2.2 (GND)
unnamed: J1.2, R1.2
unnamed: J1.6, R16.2
unnamed: J1.8, R17.2
unnamed: J1.10, R12.2
unnamed: J1.12, R11.2
unnamed: J1.14, R13.2
unnamed: J1.16, R4.2
unnamed: J1.18, R5.2
unnamed: J1.20, R3.2
unnamed: J1.22, R9.2
unnamed: J1.24, R8.2
unnamed: J1.26, R2.2
unnamed: J1.28, R7.2
unnamed: J1.30, R6.2
unnamed: J1.32, R10.2
unnamed: J1.34, R14.2
unnamed: J1.36, R15.2
VDD: C37.2, J1.37, J1.38, J1.39, J1.40, R18.2, U2.1 (IN), U2.3 (EN)

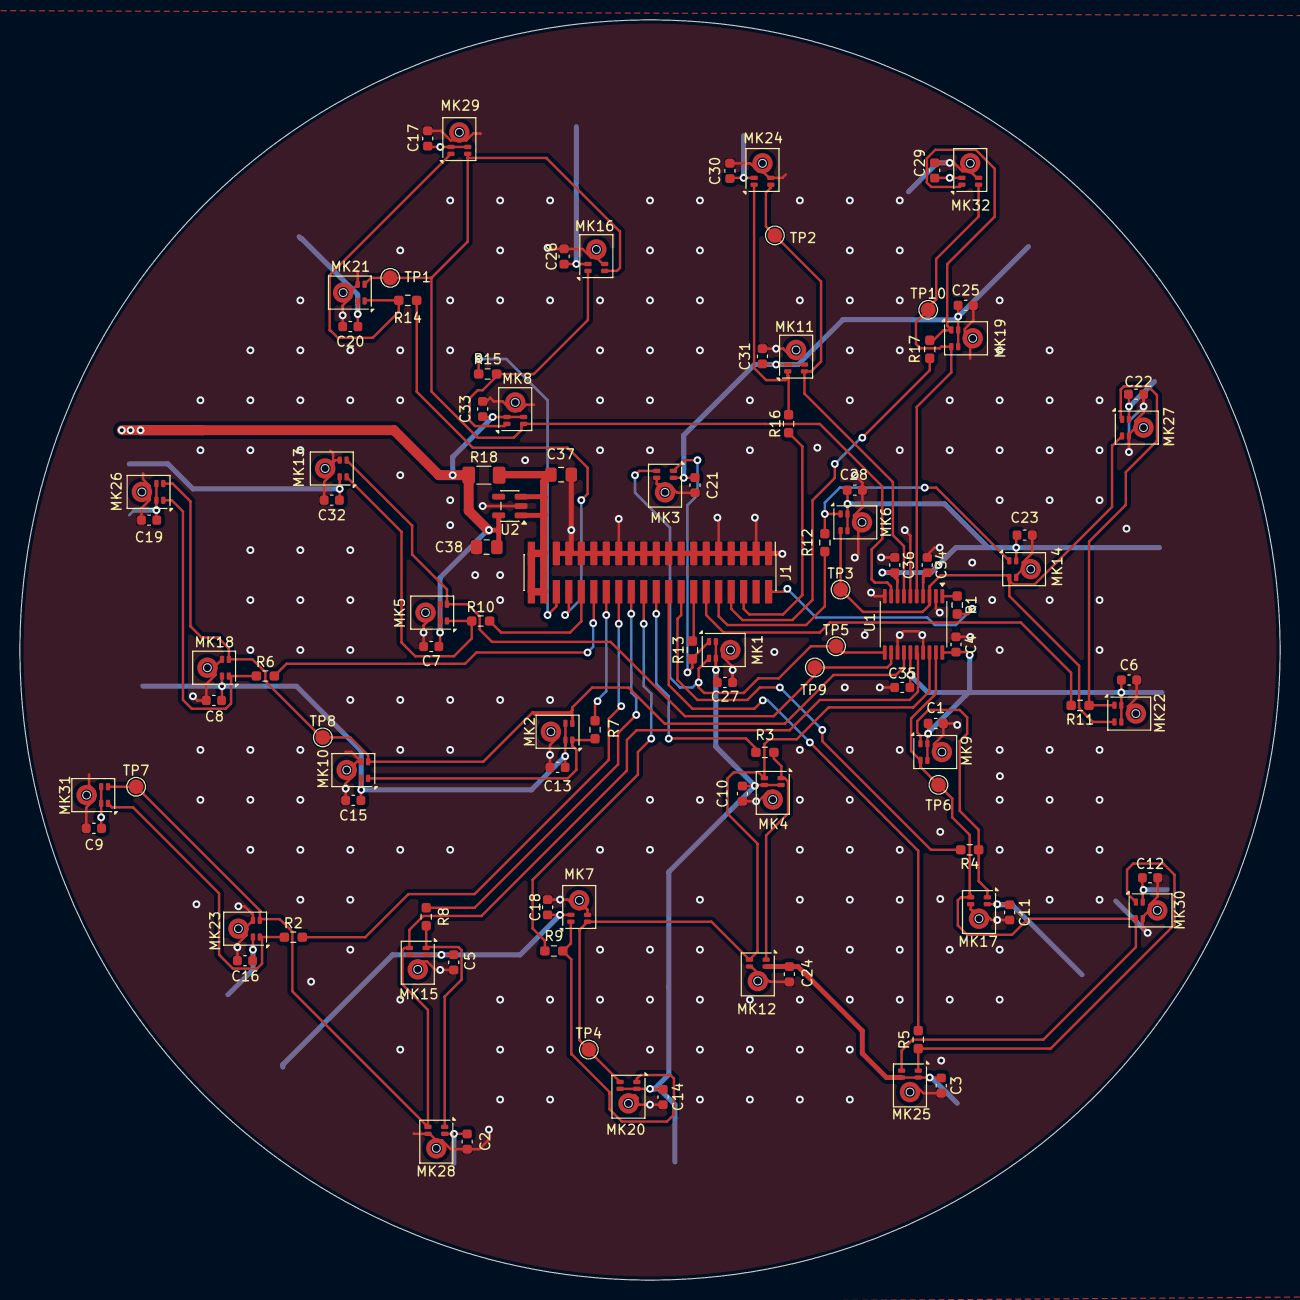
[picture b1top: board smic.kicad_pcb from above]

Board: 2 copper layers, 128.2 x 128.2 mm, 101 parts (0 on the bottom side), 47 nets.
